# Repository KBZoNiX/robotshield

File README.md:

# Robotshield V2.1 — ESETP N°703

Proyecto de programación de robots educativos sobre la placa **Robotshield V2.1** (shield para Arduino UNO). Cada grupo arma uno de estos dos robots y le carga su programa correspondiente:

- 🎮 **Fútbol** — controlado a distancia por Bluetooth desde el celular.
- 🤖 **Mini Sumo** — autónomo, busca al rival y evita salirse del ring.

## Qué hay en este repositorio

```
robotshield/
├── ROBOTSHIELD_V2.1_CONTEXTO_TECNICO.md   → mapa de pines y hardware de la placa
├── docs/
│   └── FSD.md                             → diseño completo de los dos programas
├── hardware/                              → esquemático, PCB y BOM (KiCad)
└── src/
    ├── Futbol/Futbol.ino                  → programa del robot de Fútbol
    ├── MiniSumo/MiniSumo.ino              → programa del robot de Mini Sumo
    └── TestPlaca/TestPlaca.ino            → test de la placa antes del armado final
```

Si algo de este README no alcanza para entender una decisión de diseño (por qué un pin es tal cosa, por qué el robot se comporta así), la explicación completa está en **`docs/FSD.md`**.

---

## 1. Lo que necesitás antes de empezar

- **Arduino IDE** (versión 2.x) instalado en la notebook del grupo. Descarga: https://www.arduino.cc/en/software
- Cable USB para conectar el Arduino UNO a la notebook.
- El Robotshield ya armado y con el DRV8833 enchufado (J5/J6).
- Batería para el robot — **⚠️ no debe superar los 10V** (ver `ROBOTSHIELD_V2.1_CONTEXTO_TECNICO.md`).
- **Fútbol:** módulo HC-05 enchufado en J4, y en el celular alguna app de terminal Bluetooth (o joystick simple que mande caracteres por Bluetooth clásico — no BLE).
- **Mini Sumo:** sensor HC-SR04 en J2 y los tres sensores de línea/borde en J9/J10/J11.

No hace falta instalar ninguna librería adicional: los dos programas usan solamente funciones estándar de Arduino.

---

## 2. Configurar el Arduino IDE (una sola vez por notebook)

1. Abrir el Arduino IDE.
2. Conectar el Arduino UNO por USB.
3. Arriba, en el selector de placa, elegir **Arduino Uno**.
4. Al lado, elegir el **puerto serie** donde apareció el Arduino (en Windows suele ser `COMx`, en Linux/Mac `/dev/ttyUSBx` o `/dev/cu.usbmodemxxxx`).

Si el Arduino no aparece en la lista de puertos, probar con otro cable USB (muchos cables solo cargan y no transmiten datos) o reinstalar el driver CH340/FTDI según el clon de Arduino que tengan.

---

## 3. Robot de Fútbol

### 3.1 Antes de subir el programa

**⚠️ Desconectar el HC-05 del Robotshield antes de subir el sketch por USB.** El módulo Bluetooth está cableado directo a los pines D0/D1, que son los mismos que usa el Arduino para programarse por USB — si el HC-05 queda enchufado, la carga va a fallar o quedarse colgada.

### 3.2 Subir el sketch

1. Abrir `src/Futbol/Futbol.ino` con el Arduino IDE (doble clic al archivo).
2. Con el HC-05 desconectado, hacer clic en **Subir** (flecha →).
3. Esperar el mensaje de "Subida completa".
4. **Volver a conectar el HC-05** al Robotshield.

### 3.3 Probar el control remoto

1. En el celular, emparejar el HC-05 por Bluetooth (contraseña por defecto suele ser `1234` o `0000`).
2. Abrir la app de terminal Bluetooth y conectarse al HC-05.
3. Mandar estos caracteres, uno por vez, y verificar que el robot responda:

| Carácter | Acción esperada |
|---|---|
| `F` | Avanza |
| `B` | Retrocede |
| `L` | Gira a la izquierda |
| `R` | Gira a la derecha |
| `S` | Se detiene |
| `H` | Suena la bocina |

4. Si el robot dobla para el lado contrario al que esperaban, es la asignación de motor izquierdo/derecho la que está invertida. En el código, cerca del principio, están los `#define PIN_MOTOR_IZQ_A` etc. — ver el comentario ahí mismo para saber cómo corregirlo.
5. El botón físico en D2 (SW2) hace sonar la bocina, y el botón en D12 (SW3) activa/desactiva el modo turbo (más velocidad, LED D13 prendido mientras está activo).

Más detalle del protocolo y del diseño en `docs/FSD.md`, sección 3.

---

## 4. Robot de Mini Sumo

### 4.1 Subir el sketch

1. Abrir `src/MiniSumo/MiniSumo.ino` con el Arduino IDE.
2. Conectar el Arduino por USB y subirlo con **Subir** (no hace falta desconectar nada para este robot).

### 4.2 Calibrar los sensores de borde (obligatorio antes de competir)

Los sensores de línea/borde vienen con un umbral de fábrica en el código (`UMBRAL_BORDE`) que **casi seguro no va a servir tal cual** para la superficie real de la cancha. Hay que calibrarlo:

1. En el código, cambiar la línea `const bool MODO_DEBUG_SENSORES = false;` a `true`.
2. Volver a subir el sketch.
3. Abrir el **Monitor Serie** del Arduino IDE (velocidad 9600).
4. Con el robot apoyado sobre la superficie negra de la cancha, anotar los tres valores que aparecen.
5. Apoyar el robot sobre la línea blanca del borde y anotar los tres valores de nuevo.
6. Elegir un valor de `UMBRAL_BORDE` que quede a mitad de camino entre lo que midieron sobre negro y sobre blanco.
7. Volver a poner `MODO_DEBUG_SENSORES` en `false` y subir el sketch de nuevo (con el Monitor Serie abierto el robot gasta tiempo mandando texto en vez de reaccionar rápido — para competir tiene que quedar en `false`).

### 4.3 Verificar la ubicación de los sensores

En el código, `SENSOR_BORDE_IZQUIERDO`, `SENSOR_BORDE_DERECHO` y `SENSOR_BORDE_FRONTAL` asumen dónde está montado cada sensor en el chasis. Confirmar que coincide con cómo armó cada grupo su robot; si no, cambiar los pines (A1/A2/A3) en esos `#define` para que coincidan con la ubicación real.

### 4.4 Cómo correrlo

1. Apoyar el robot en el ring.
2. Apretar el botón D2 (SW2) para armarlo.
3. El robot va a hacer una cuenta regresiva de 5 bips (no se mueve todavía) y después arranca a buscar solo.
4. El botón D12 (SW3) funciona en cualquier momento como **parada de emergencia**: lo detiene y lo vuelve a dejar esperando. Probarlo antes de la primera prueba en cancha.

Más detalle de la máquina de estados (búsqueda, ataque, evasión) en `docs/FSD.md`, sección 4.

---

## 5. Test de placa (antes del armado final)

Antes de armar el robot definitivo, conviene probar que el Robotshield ya soldado/cableado funciona: LEDs, pulsadores, sensor ultrasónico, motores y módulo Bluetooth. Para eso está `src/TestPlaca/TestPlaca.ino`, que prueba todo eso en un solo programa corto, sin depender de la lógica de Fútbol ni de Mini Sumo.

### 5.1 Subir el sketch

1. Si el HC-05 está conectado, **desconectarlo** — comparte los pines D0/D1 con el Monitor Serie, y si queda enchufado la carga por USB puede fallar (mismo motivo que en el robot de Fútbol).
2. Abrir `src/TestPlaca/TestPlaca.ino` con el Arduino IDE y subirlo.
3. Abrir el **Monitor Serie** a **9600 baudios**.

### 5.2 Qué esperar

Al arrancar, el programa corre solo, una sola vez, narrando cada paso por el Monitor Serie:

1. **LEDs** — se prenden en secuencia (D4, D7, D13). Verificar que los tres enciendan.
2. **Pulsadores** — pide apretar el botón D2 y después el D12 (10 segundos de margen cada uno). Si no detecta el apriete a tiempo, avisa "no se detectó, revisar cableado".
3. **Sensor ultrasónico** — hace 5 mediciones de distancia y las imprime en cm. Si dice "sin eco", revisar que el HC-SR04 esté bien conectado.
4. **Motores** — cada motor gira adelante y atrás brevemente. Confirmar visualmente que los dos giran en el sentido esperado.

Para repetir estos cuatro tests, alcanza con resetear la placa (botón reset del Arduino).

### 5.3 Test de Bluetooth

Al terminar la secuencia automática, el programa queda esperando caracteres por Serial indefinidamente (no hace falta resetear para esto):

- **Sin HC-05 a mano todavía:** escribir cualquier cosa en el Monitor Serie y enviarla — el Arduino la devuelve (eco), prende un LED y hace un beep. Sirve como prueba rápida aunque no tengan el módulo Bluetooth conectado.
- **Con el HC-05:** volver a conectarlo al Robotshield, emparejarlo desde el celular con una app de terminal Bluetooth, y mandar caracteres desde ahí — deberían aparecer de vuelta en la app (eco) junto con el LED y el beep.

---

## 6. Problemas comunes

| Problema | Posible causa |
|---|---|
| La carga del sketch de Fútbol falla o se cuelga | El HC-05 sigue conectado — desenchufarlo y volver a intentar |
| El robot no aparece en la lista de puertos | Cable USB solo de carga, o falta el driver del chip USB-serie |
| El robot dobla para el lado contrario | Asignación motor izquierdo/derecho invertida — ver comentario en el código junto a los `#define` de motores |
| El Mini Sumo se sale del ring o no reacciona a la línea | `UMBRAL_BORDE` mal calibrado, o los sensores están asignados al pin equivocado — repetir el paso 4.2 |
| El HC-05 no aparece para emparejar | Verificar alimentación (LED del HC-05 titilando) y que esté en J4 con la polaridad correcta |

Para cualquier otra duda sobre el diseño del código (por qué está estructurado así, qué hace cada función), la referencia completa es `docs/FSD.md`.

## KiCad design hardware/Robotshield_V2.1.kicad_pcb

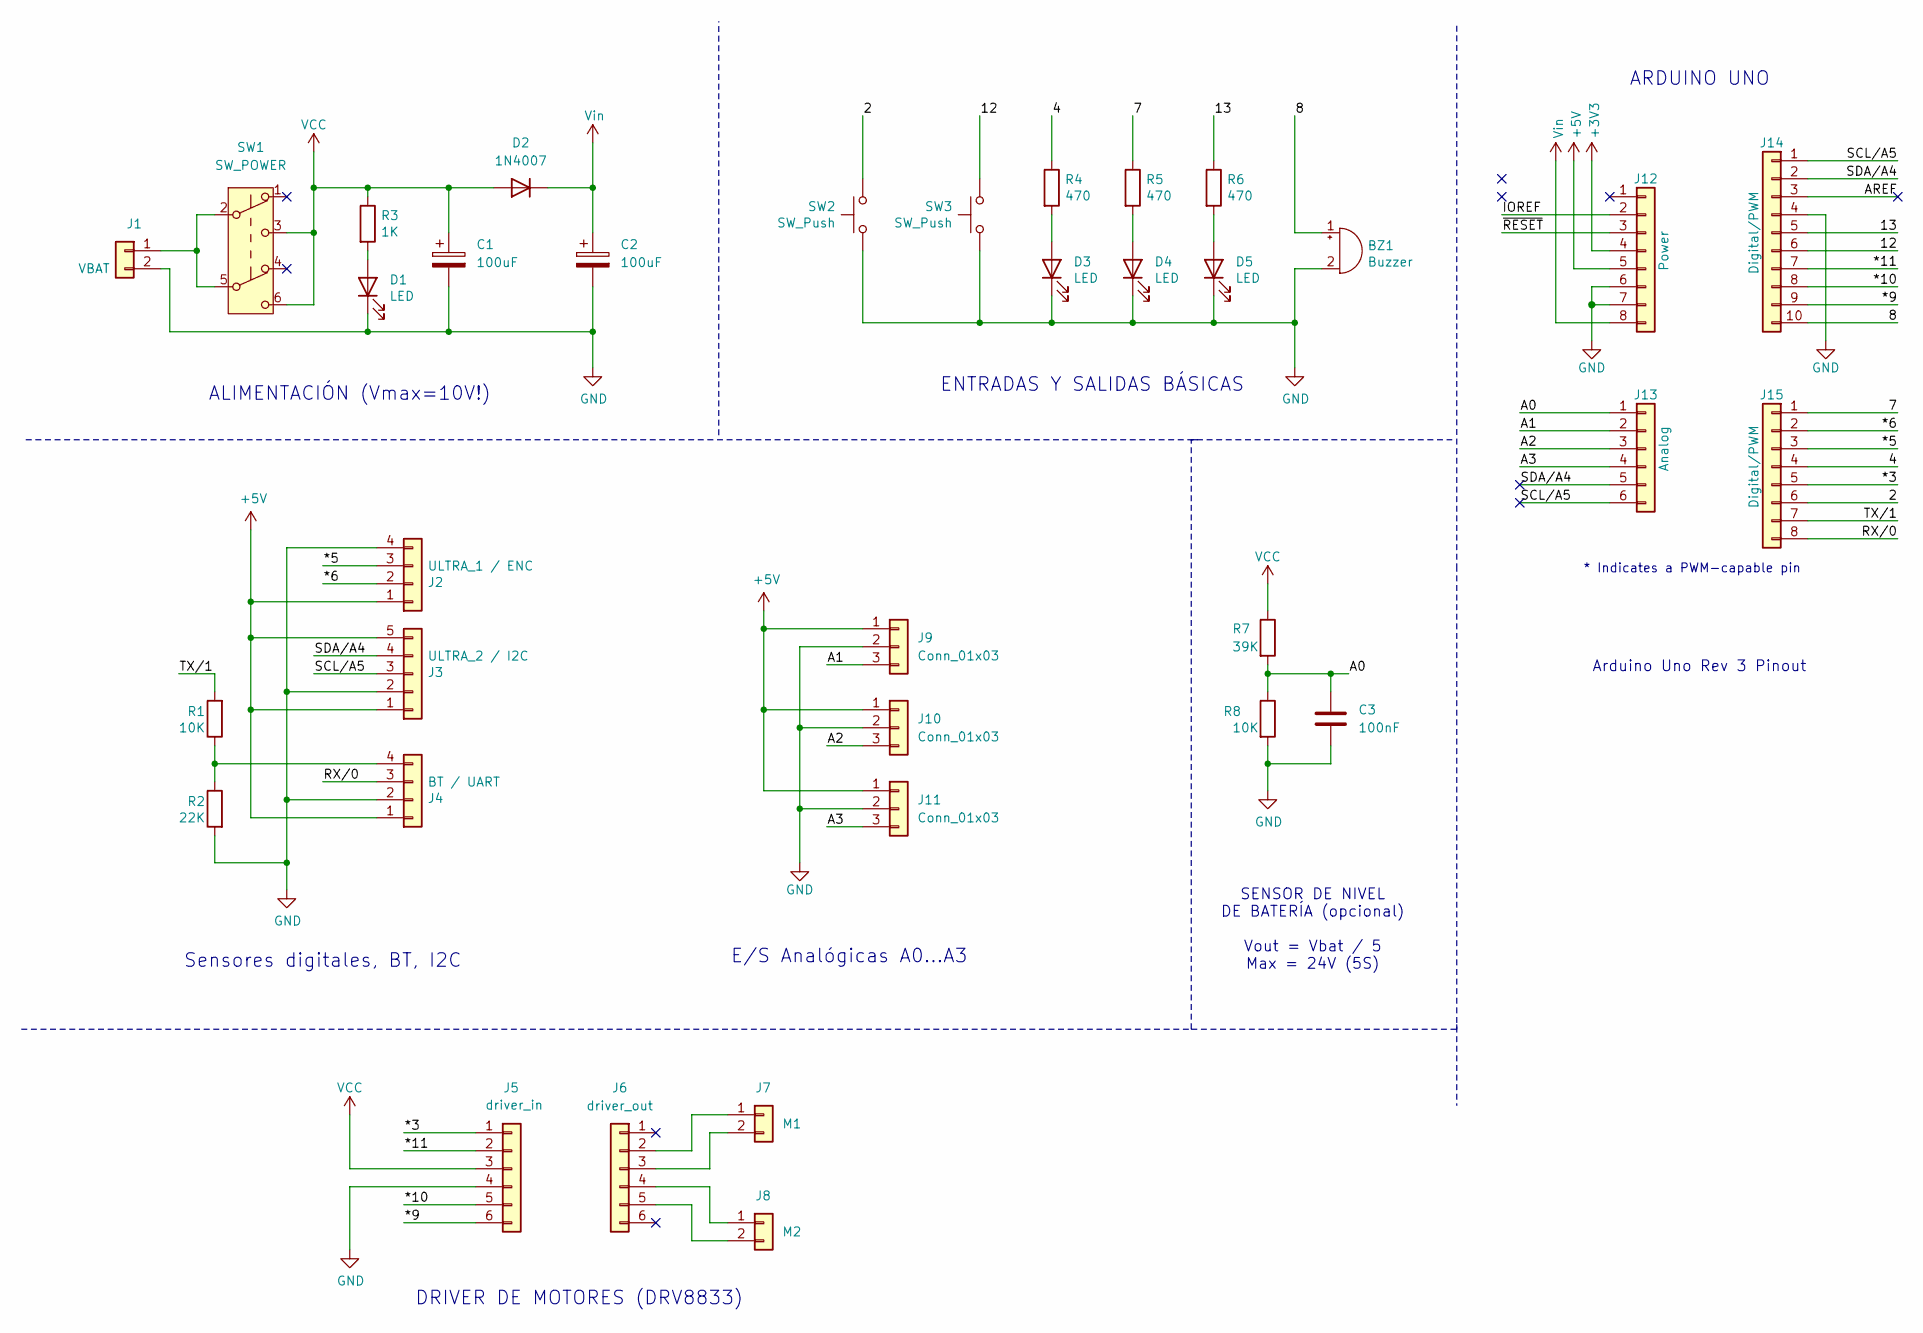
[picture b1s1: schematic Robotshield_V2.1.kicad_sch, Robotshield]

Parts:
BZ1: Buzzer; Buzzer_12x9.5RM7.6
C1, C2: 100uF; CP_Radial_D5.0mm_P2.00mm
C3: 100nF; C_0805_2012Metric_Pad1.18x1.45mm_HandSolder
D1: LED; LED_D3.0mm_Clear
D2: 1N4007; D_DO-41_SOD81_P10.16mm_Horizontal
D3, D4, D5: LED; LED_D5.0mm
J1: VBAT; PinHeader_1x02_P2.54mm_Vertical
J2: ULTRA_1 / ENC; PinHeader_1x04_P2.54mm_Vertical
J3: ULTRA_2 / I2C; PinHeader_1x05_P2.54mm_Vertical
J4: BT / UART; PinSocket_1x04_P2.54mm_Vertical
J5: driver_in; PinSocket_1x06_P2.54mm_Vertical
J6: driver_out; PinSocket_1x06_P2.54mm_Vertical
J7: M1; PinHeader_1x02_P2.54mm_Vertical
J8: M2; PinHeader_1x02_P2.54mm_Vertical
J9, J10, J11: Conn_01x03; PinHeader_1x03_P2.54mm_Vertical
J12: Power; PinHeader_1x08_P2.54mm_Vertical
J13: Analog; PinHeader_1x06_P2.54mm_Vertical
J14: Digital/PWM; PinHeader_1x10_P2.54mm_Vertical
J15: Digital/PWM; PinHeader_1x08_P2.54mm_Vertical
R1, R8: 10K; R_0805_2012Metric_Pad1.20x1.40mm_HandSolder
R2: 22K; R_0805_2012Metric_Pad1.20x1.40mm_HandSolder
R3: 1K; R_Axial_DIN0207_L6.3mm_D2.5mm_P7.62mm_Horizontal
R4, R5, R6: 470; R_Axial_DIN0207_L6.3mm_D2.5mm_P7.62mm_Horizontal
R7: 39K; R_0805_2012Metric_Pad1.20x1.40mm_HandSolder
SW1: SW_POWER; SW_Push_2P2T_Toggle_7x7mm
SW2, SW3: SW_Push; SW_PUSH_6mm

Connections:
+3V3: J12.4
+5V: J2.1, J3.1, J3.5, J4.1, J9.1, J10.1, J11.1, J12.5
/2: J15.6, SW2.1
/4: J15.4, R4.1
/7: J15.1, R5.1
/8: BZ1.1 (-), J14.10
/12: J14.6, SW3.1
/13: J14.5, R6.1
/*3: J5.1, J15.5
/*5: J2.3, J15.3
/*6: J2.2, J15.2
/*9: J5.6, J14.9
/*10: J5.5, J14.8
/*11: J5.2, J14.7
/A0: C3.1, J13.1, R7.2, R8.1
/A1: J9.3, J13.2
/A2: J10.3, J13.3
/A3: J11.3, J13.4
/AREF: J14.3
/IOREF: J12.2
/RX/0: J4.3, J15.8
/SCL/A5: J3.3, J13.6, J14.1
/SDA/A4: J3.4, J13.5, J14.2
/TX/1: J15.7, R1.2
/~RESET: J12.3
GND: BZ1.2 (+), C1.2, C2.2, C3.2, D1.1 (K), D3.1 (K), D4.1 (K), D5.1 (K), J1.2, J2.4, J3.2, J4.2, J5.4, J9.2, J10.2, J11.2, J12.6, J12.7, J14.4, R2.2, R8.2, SW2.2, SW3.2
unnamed: D1.2 (A), R3.2
unnamed: D3.2 (A), R4.2
unnamed: D4.2 (A), R5.2
unnamed: D5.2 (A), R6.2
unnamed: J1.1, SW1.2 (B), SW1.5 (B)
unnamed: J4.4, R1.1, R2.1
unnamed: J6.2, J7.1
unnamed: J6.3, J7.2
unnamed: J6.4, J8.1
unnamed: J6.5, J8.2
VCC: C1.1, D2.2 (A), J5.3, R3.1, R7.1, SW1.3 (C), SW1.6 (C)
Vin: C2.1, D2.1 (K), J12.8

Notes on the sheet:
E/S Analógicas A0...A3
Arduino Uno Rev 3 Pinout
Sensores digitales, BT, I2C
ALIMENTACIÓN (Vmax=10V!)
SENSOR DE NIVEL DE BATERÍA (opcional) Vout = Vbat / 5 Max = 24V (5S)
ARDUINO UNO
DRIVER DE MOTORES (DRV8833)
* Indicates a PWM-capable pin
ENTRADAS Y SALIDAS BÁSICAS

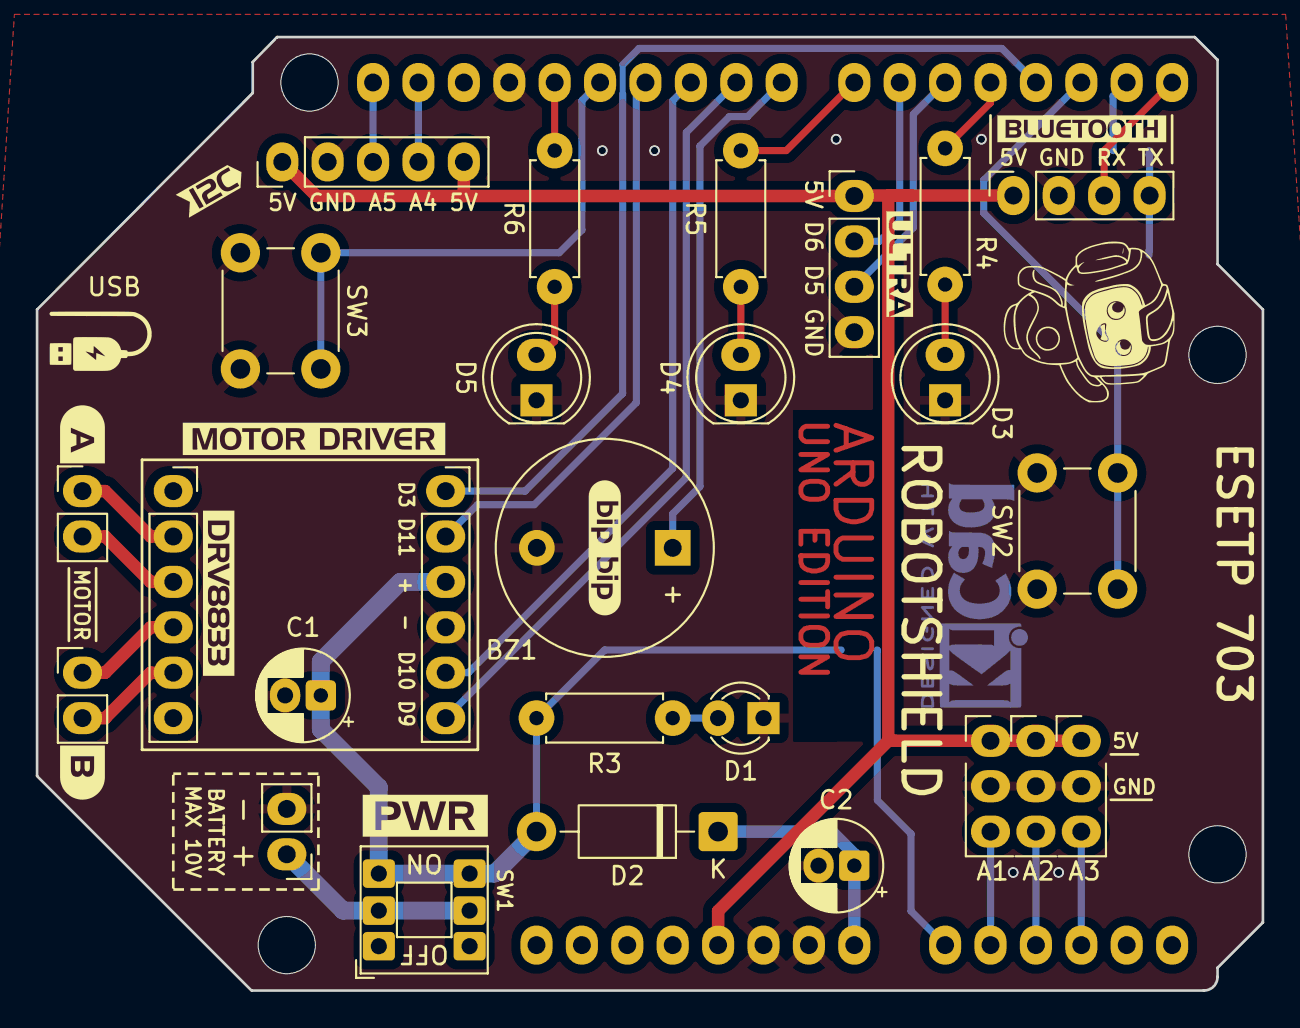
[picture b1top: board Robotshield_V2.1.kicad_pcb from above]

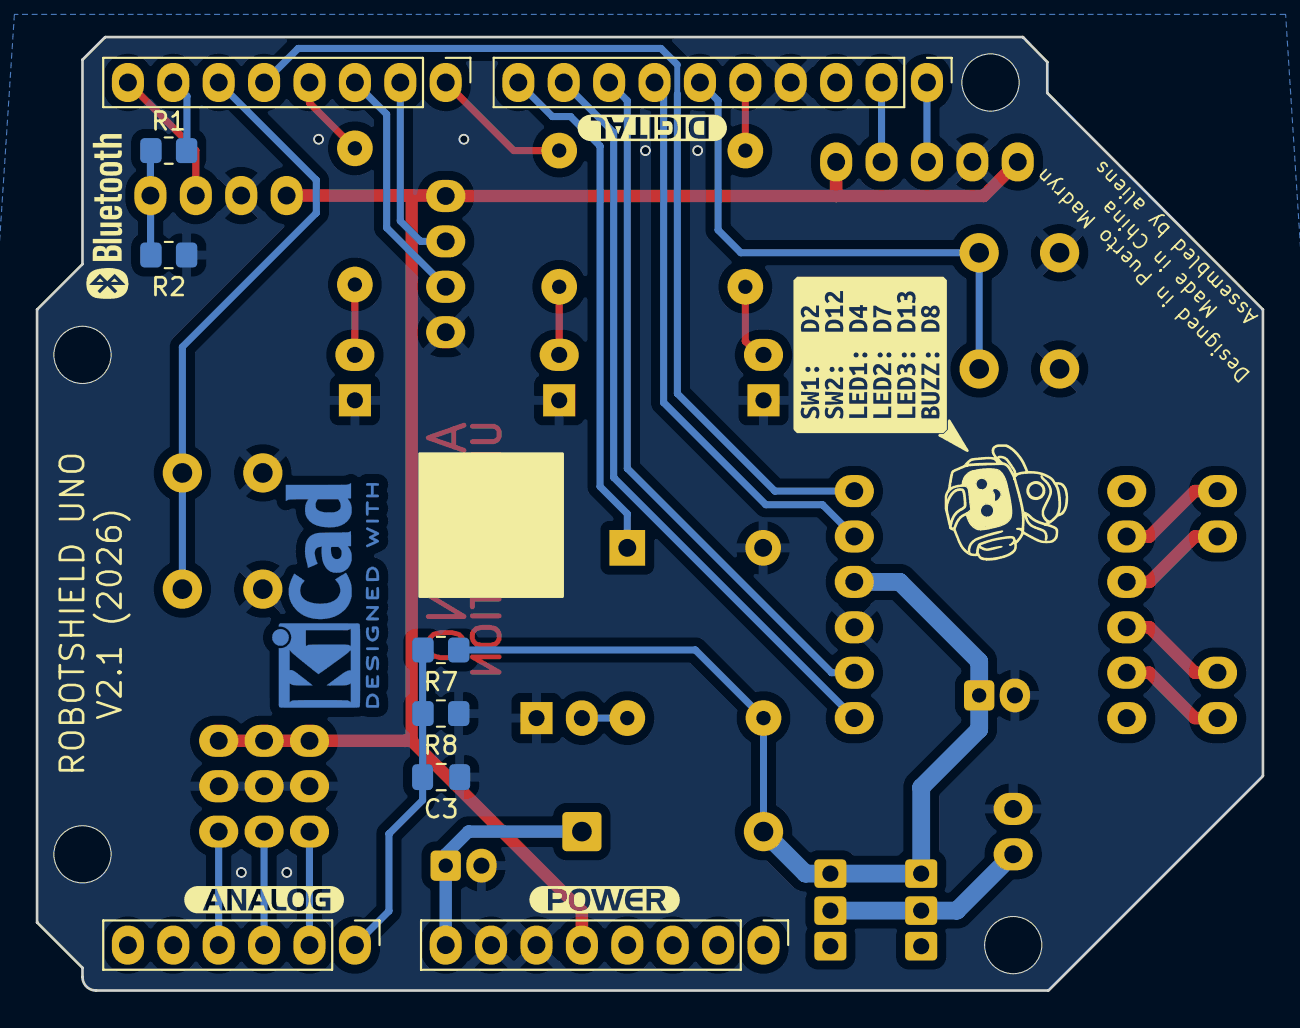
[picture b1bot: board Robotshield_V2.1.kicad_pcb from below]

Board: 2 copper layers, 68.6 x 53.3 mm, 52 parts (13 on the bottom side), 34 nets.

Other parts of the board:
MH1, MH2, MH3, MH4: MountingHole_3.2mm
kibuzzard-6A53D98A: G***; kibuzzard-6A53D98A
kibuzzard-6A53E27C: G***; kibuzzard-6A53E27C
kibuzzard-6A53E41F: G***; kibuzzard-6A53E41F
kibuzzard-6A53E214: G***; kibuzzard-6A53E214
kibuzzard-6A53E243: G***; kibuzzard-6A53E243
kibuzzard-6A53E518: G***; kibuzzard-6A53E518
kibuzzard-6A53ED8F: G***; kibuzzard-6A53ED8F
kibuzzard-6A53EDDA: G***; kibuzzard-6A53EDDA
kibuzzard-6A53F17D: G***; kibuzzard-6A53F17D
kibuzzard-6850FB1B: G***; kibuzzard-6850FB1B
kibuzzard-675711CB: G***; kibuzzard-675711CB
kibuzzard-675711D0: G***; kibuzzard-675711D0
kibuzzard-6852314D: G***; kibuzzard-6852314D

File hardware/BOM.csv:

"Id";"Identificador";"Huella";"Cantidad";"Identificación";"Suministrador y ref";
1;"C1,C2";"CP_Radial_D5.0mm_P2.00mm";2;"100uF";;;
2;"SW3,SW2";"SW_PUSH_6mm";2;"SW_Push";;;
3;"D1";"LED_D3.0mm_Clear";1;"LED";;;
4;"D5,D4,D3";"LED_D5.0mm";3;"LED";;;
5;"J3";"PinHeader_1x05_P2.54mm_Vertical";1;"ULTRA_2 / I2C";;;
6;"J11,J9,J10";"PinHeader_1x03_P2.54mm_Vertical";3;"Conn_01x03";;;
7;"J1";"PinHeader_1x02_P2.54mm_Vertical";1;"VBAT";;;
8;"J5";"PinSocket_1x06_P2.54mm_Vertical";1;"driver_in";;;
9;"BZ1";"Buzzer_12x9.5RM7.6";1;"Buzzer";;;
10;"R4,R5,R6";"R_Axial_DIN0207_L6.3mm_D2.5mm_P7.62mm_Horizontal";3;"470";;;
11;"J2";"PinHeader_1x04_P2.54mm_Vertical";1;"ULTRA_1 / ENC";;;
12;"R3";"R_Axial_DIN0207_L6.3mm_D2.5mm_P7.62mm_Horizontal";1;"1K";;;
13;"J4";"PinSocket_1x04_P2.54mm_Vertical";1;"BT / UART";;;
14;"J8";"PinHeader_1x02_P2.54mm_Vertical";1;"M2";;;
15;"J7";"PinHeader_1x02_P2.54mm_Vertical";1;"M1";;;
16;"J6";"PinSocket_1x06_P2.54mm_Vertical";1;"driver_out";;;
17;"D2";"D_DO-41_SOD81_P10.16mm_Horizontal";1;"1N4007";;;
18;"SW1";"SW_Push_2P2T_Toggle_7x7mm";1;"SW_POWER";;;
19;"J12";"PinHeader_1x08_P2.54mm_Vertical";1;"Power";;;
20;"J13";"PinHeader_1x06_P2.54mm_Vertical";1;"Analog";;;
21;"J14";"PinHeader_1x10_P2.54mm_Vertical";1;"Digital/PWM";;;
22;"J15";"PinHeader_1x08_P2.54mm_Vertical";1;"Digital/PWM";;;
23;"C3";"C_0805_2012Metric_Pad1.18x1.45mm_HandSolder";1;"100nF";;;
24;"R1,R8";"R_0805_2012Metric_Pad1.20x1.40mm_HandSolder";2;"10K";;;
25;"R2";"R_0805_2012Metric_Pad1.20x1.40mm_HandSolder";1;"22K";;;
26;"R7";"R_0805_2012Metric_Pad1.20x1.40mm_HandSolder";1;"39K";;;
